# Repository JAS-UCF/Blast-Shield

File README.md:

# Blast-Shield

PCB Design for WARHEAD

## See the BOM
[https://jas-ucf.github.io/Blast-Shield/]

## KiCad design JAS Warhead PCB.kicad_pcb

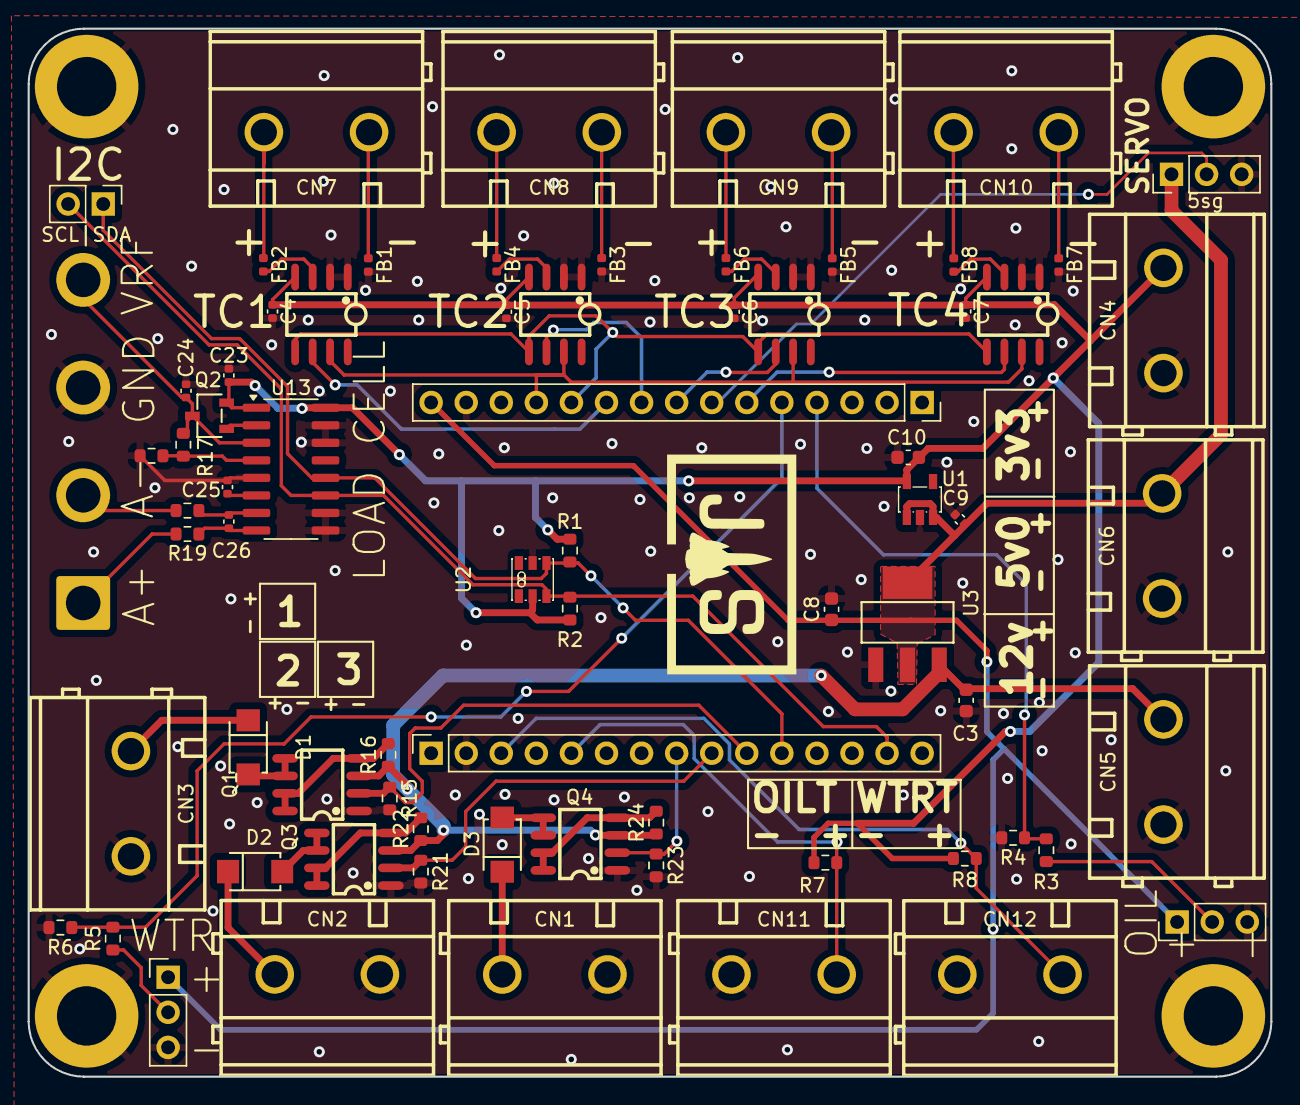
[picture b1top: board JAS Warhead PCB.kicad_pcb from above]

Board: 2 copper layers, 90.0 x 75.9 mm, 76 parts (0 on the bottom side), 51 nets.

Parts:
C3, C8, C10: 10uF; C_0603_1608Metric
C4, C5, C6, C7, C25: 100nF; C_0402_1005Metric
C9: 1uF; C_0402_1005Metric
C23, C24: 10uF; C_0402_1005Metric
C26: 0.1uF; C_0402_1005Metric
CN1, CN2, CN3, CN4, CN5, CN6, CN7, CN8, CN9, CN10, CN11, CN12: DB910-7.62-2P; CONN-TH_2P-P7.62_DB910-7.62-2P
D1, D2, D3: M7F_C466485; SMAF_L3.5-W2.6-LS4.7-RD
FB1, FB2, FB3, FB4, FB5, FB6, FB7, FB8: FerriteBead; L_0402_1005Metric
H1, H2, H3, H4: MountingHole_Pad; MountingHole_4.3mm_M4_DIN965_Pad
J1, J5, J6: Conn_01x03_Pin; PinHeader_1x03_P2.54mm_Vertical
J3: Conn_01x02_Pin; PinHeader_1x02_P2.54mm_Vertical
J9, J10: Conn_01x15_Socket; PinSocket_1x15_P2.54mm_Vertical
J15: Conn_01x04_Socket; SolderWire-2sqmm_1x04_P7.8mm_D2mm_OD3.9mm
Q1, Q3, Q4: WSP4606; SOP-8_L4.9-W3.9-P1.27-LS6.0-BL
Q2: S8550M-D; SOT-23-3_L2.9-W1.6-P1.90-LS2.8-BR
R1, R2, R17, R18: 1K; R_0603_1608Metric
R3, R5: 5K; R_0603_1608Metric
R4, R6: 2K; R_0603_1608Metric
R7, R8, R15, R16, R21, R22, R23, R24: 10K; R_0603_1608Metric
R19, R20: 100; R_0603_1608Metric
U1: SE5218ALG-LF; SOT-23-5_L3.0-W1.7-P0.95-LS2.8-BR
U2: AHT20-F; SENSOR-SMD-6_AHT20
U3: LM1117S-5.0; SOT-223-3_L6.5-W3.4-P2.30-LS7.0-BR
U6, U8, U10, U12: MAX6675ISA+T; SOIC-8_L5.0-W4.0-P1.27-LS6.0-BL
U13: HX711; SOP-16_3.9x9.9mm_P1.27mm

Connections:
+3V3: C4.1, C5.1, C6.1, C7.1, C10.1, C23.2, CN4.2, Q2.2 (E), R1.2, R2.1, R7.1, R8.1, U1.5 (VOUT), U2.2 (VDD), U6.4 (VCC), U8.4 (VCC), U10.4 (VCC), U12.4 (VCC), U13.1 (VSUP), U13.16 (DVDD)
+5V: C8.1, C9.1, CN6.2, J1.1, J5.1, J6.1, J9.15, U1.1 (VIN), U1.3 (ENABLE), U3.2 (OUT), U3.4 (TAB)
+12V: C3.1, CN5.2, Q1.3 (S2), Q3.3 (S2), Q4.3 (S2), R16.1, R22.1, R24.1, U3.3 (IN)
/CS1: J9.10, U6.6 (~CS)
/CS2: J9.9, U8.6 (~CS)
/CS3: J9.8, U10.6 (~CS)
/CS4: J9.6, U12.6 (~CS)
/OIL_Press: J9.4, R3.2, R4.1
/OilTemp: CN11.2, J10.5, R7.2
/RELAY1: J10.10, Q1.2 (G1), R15.1
/RELAY2: J10.9, Q3.2 (G1), R21.1
/RELAY3: J10.8, Q4.2 (G1), R23.1
/RELAY+CONTROLLER1/VOUT: CN2.1, D2.1 (C)
/RELAY+CONTROLLER2/VOUT: CN1.1, D3.1 (C)
/RELAY+CONTROLLER/VOUT: CN3.1, D1.1 (C)
/SCL: J3.2, J10.14, R2.2, U2.3 (SCL), U13.11 (PD_SCK)
/SDA: J3.1, J10.11, R1.1, U2.4 (SDA), U13.12 (DOUT)
/SERVO: J1.2, J9.7
/SPI CLK: J9.11, U6.5 (SCK), U8.5 (SCK), U10.5 (SCK), U12.5 (SCK)
/SPI Data_In: J9.12, U6.7 (SO), U8.7 (SO), U10.7 (SO), U12.7 (SO)
/WTR_Press: J9.5, R5.2, R6.1
/WtrTemp: CN12.2, J10.3, R8.2
GND: C3.2, C4.2, C5.2, C6.2, C7.2, C8.2, C9.2, C10.2, C23.1, C24.1, C25.2, CN1.2, CN2.2, CN3.2, CN4.1, CN5.1, CN6.1, CN11.1, CN12.1, FB1.2, FB3.2, FB5.2, FB7.2, H1.1, H2.1, H3.1, H4.1, J1.3, J5.3, J6.3, J9.14, J10.2, J15.3, Q1.1 (S1), Q3.1 (S1), Q4.1 (S1), R4.2, R6.2, R15.2, R18.2, R21.2, R23.2, U1.2 (GND), U2.5 (GND), U3.1 (ADJ/GND), U6.1 (GND), U6.2 (T-), U8.1 (GND), U8.2 (T-), U10.1 (GND), U10.2 (T-), U12.1 (GND), U12.2 (T-), U13.5 (AGND), U13.9 (INB-), U13.10 (INB+), U13.14 (XI), U13.15 (RATE)
unnamed: CN7.1, FB1.1
unnamed: CN7.2, FB2.1
unnamed: CN8.1, FB3.1
unnamed: CN8.2, FB4.1
unnamed: CN9.1, FB5.1
unnamed: CN9.2, FB6.1
unnamed: CN10.1, FB7.1
unnamed: CN10.2, FB8.1
unnamed: D1.2 (A), Q1.5 (D2), Q1.6 (D2)
unnamed: D2.2 (A), Q3.5 (D2), Q3.6 (D2)
unnamed: D3.2 (A), Q4.5 (D2), Q4.6 (D2)
unnamed: J5.2, R3.1
unnamed: J6.2, R5.1
unnamed: J15.1, R19.1
unnamed: J15.2, R20.1
unnamed: C24.2, J15.4, Q2.3 (C), R17.1, U13.3 (AVDD)
unnamed: Q1.4 (G2), Q1.7 (D1), Q1.8 (D1), R16.2
unnamed: Q2.1 (B), U13.2 (BASE)
unnamed: Q3.4 (G2), Q3.7 (D1), Q3.8 (D1), R22.2
unnamed: Q4.4 (G2), Q4.7 (D1), Q4.8 (D1), R24.2
unnamed: FB2.2, U6.3 (T+)
unnamed: FB4.2, U8.3 (T+)
unnamed: FB6.2, U10.3 (T+)
unnamed: FB8.2, U12.3 (T+)
unnamed: C26.2, R19.2, U13.8 (INA+)
unnamed: C26.1, R20.2, U13.7 (INA-)
unnamed: C25.1, U13.6 (VBG)
unnamed: R17.2, R18.1, U13.4 (VFB)

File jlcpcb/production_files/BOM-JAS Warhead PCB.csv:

Comment,Designator,Footprint,LCSC,Quantity
SE5218ALG-LF,U1,SOT-23-5_L3.0-W1.7-P0.95-LS2.8-BR,C118233,1
LM1117S-5.0,U3,SOT-223-3_L6.5-W3.4-P2.30-LS7.0-BR,C126028,1
10uF,"C23,C24",C_0402_1005Metric,C15525,2
MAX6675ISA+T,"U10,U12,U6,U8",SOIC-8_L5.0-W4.0-P1.27-LS6.0-BL,C16030,4
1K,"R1,R17,R18,R2",R_0603_1608Metric,C21190,4
FerriteBead,"FB1,FB2,FB3,FB4,FB5,FB6,FB7,FB8",L_0402_1005Metric,C21516,8
100,"R19,R20",R_0603_1608Metric,C22775,2
2K,"R4,R6",R_0603_1608Metric,C22975,2
5K,"R3,R5",R_0603_1608Metric,C23186,2
10K,"R15,R16,R21,R22,R23,R24,R7,R8",R_0603_1608Metric,C25804,8
AHT20-F,U2,SENSOR-SMD-6_AHT20,C3012622,1
S8550M-D,Q2,SOT-23-3_L2.9-W1.6-P1.90-LS2.8-BR,C305484,1
100nF,"C25,C26,C4,C5,C6,C7",C_0402_1005Metric,C307331,6
DB910-7.62-2P,"CN1,CN10,CN11,CN12,CN2,CN3,CN4,CN5,CN6,CN7,CN8,CN9",CONN-TH_2P-P7.62_DB910-7.62-2P,C395876,12
M7F_C466485,"D1,D2,D3",SMAF_L3.5-W2.6-LS4.7-RD,C466485,3
1uF,C9,C_0402_1005Metric,C52923,1
HX711,U13,SOP-16_3.9x9.9mm_P1.27mm,C6705483,1
WSP4606,"Q1,Q3,Q4",SOP-8_L4.9-W3.9-P1.27-LS6.0-BL,C86361,3
10uF,"C10,C3,C8",C_0603_1608Metric,C96446,3
Conn_01x15_Socket,J10,PinSocket_1x15_P2.54mm_Vertical,,1
Conn_01x02_Pin,J3,PinHeader_1x02_P2.54mm_Vertical,,1
Conn_01x15_Socket,J9,PinSocket_1x15_P2.54mm_Vertical,,1
Conn_01x04_Socket,J15,SolderWire-2sqmm_1x04_P7.8mm_D2mm_OD3.9mm,,1

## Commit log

2024-04-08 The Beginnings of Something Great
2024-04-09 adds MAX31855 SPI K-Type Thermocouple Amps
2024-04-09 finalizes MAX boards & Begins PCB Design
2024-04-09 adds labels
2024-04-09 PCB Wiring to ESP32
2024-04-13 mounting holes
2024-04-15 adds relays
2024-04-20 relays
2024-04-21 adds thermister locations
2024-04-21 new bom
2024-04-21 changes to readme
2024-04-22 adds graphics
2024-04-22 remade-bom
2024-04-22 adds test & test points
2024-04-22 regen bom
2024-05-11 remove handsolder
2024-06-11 update positioning
2024-06-11 start compliance with PCBway
2024-06-12 edits to conform to design regulation
2024-06-15 change resistors
2024-06-15 move resistors
2024-06-18 move some traces
2024-06-18 fix merge problem
2024-06-18 remake bom & fix trace proximity
2024-06-18 fix traces
2024-08-22 add JLC DB
2024-10-11 refresh stage 1
2024-10-11 lfs move
2024-10-25 progress toward final board, need smaller relays
2025-01-31 begin new bom
2025-02-01 almost there
2025-02-03 first round routing
2025-02-06 almost ready for prod
2025-02-06 update bom
2025-02-16 add servo drive?
2025-02-19 send off for prod
2025-03-16 fixes foir rev2
2025-03-22 docs
